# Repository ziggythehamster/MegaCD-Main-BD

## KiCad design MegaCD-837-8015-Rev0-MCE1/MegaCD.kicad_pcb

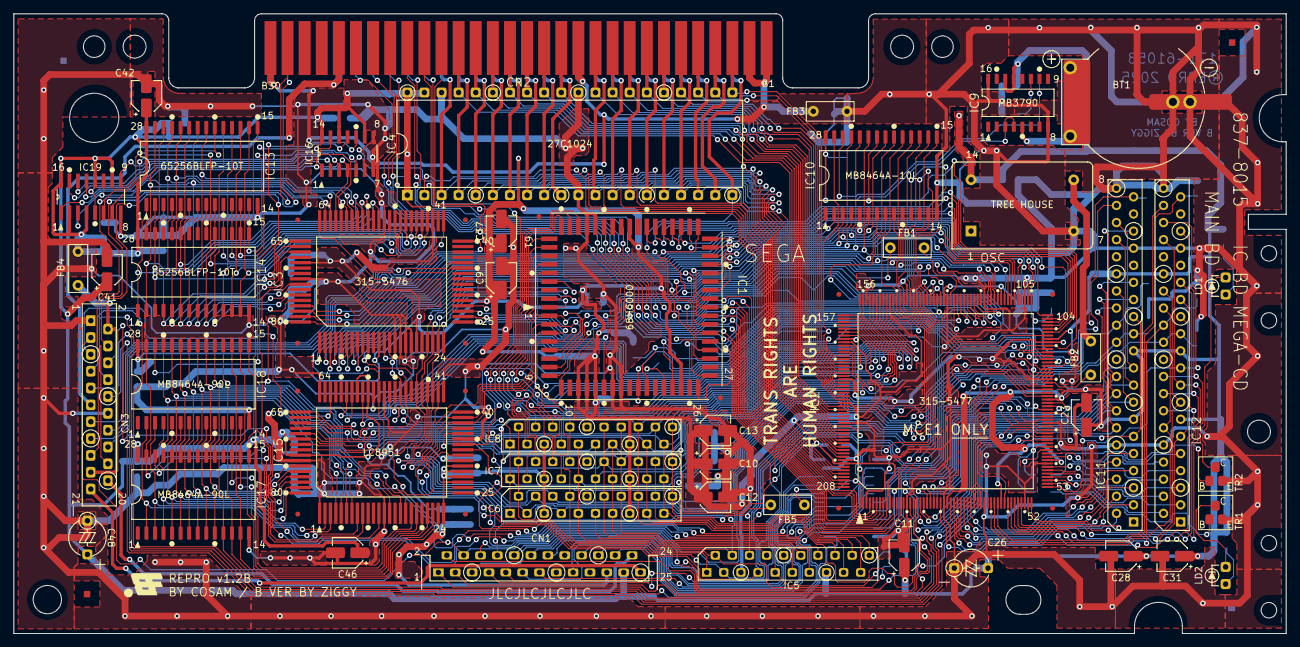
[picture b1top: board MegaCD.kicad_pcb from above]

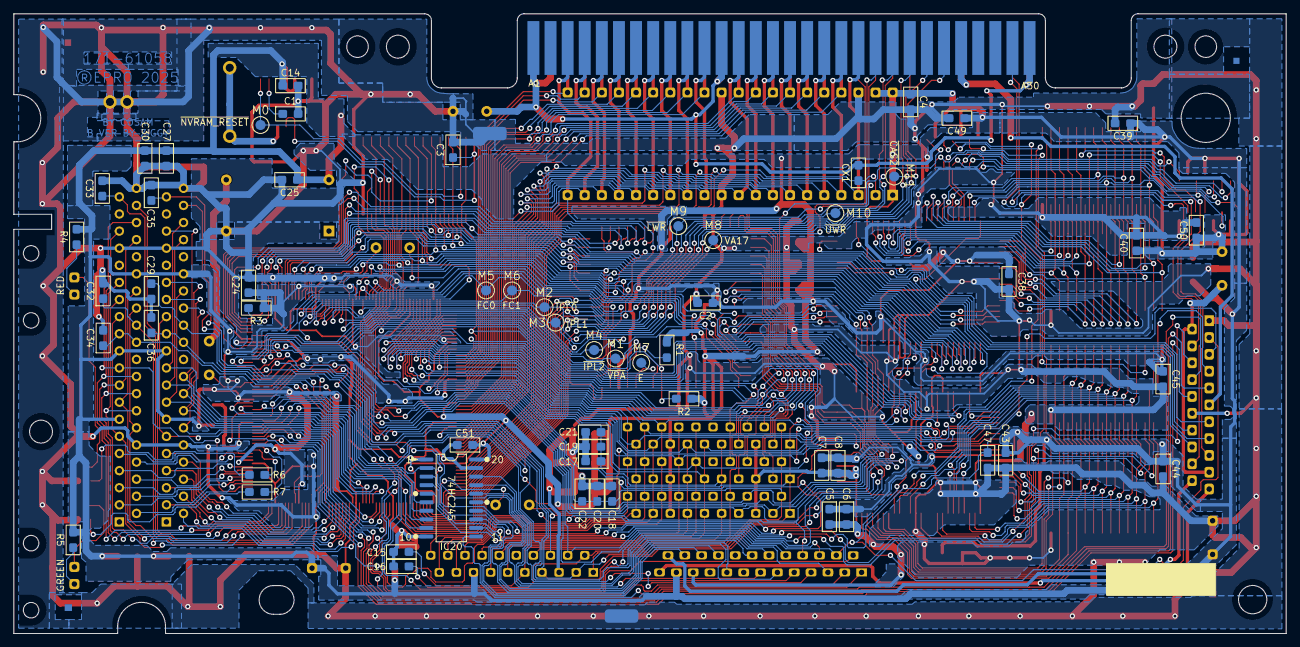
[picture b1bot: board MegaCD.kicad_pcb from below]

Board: 6 copper layers, 188.9 x 92.0 mm, 107 parts (60 on the bottom side), 274 nets.

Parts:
BT1: AL2032; Battery
C1: 1000pF; SMD_0805_HandSolder_Medium
C2, C3, C4, C5, C6, C7, C8, C14, C24, C25, C27, C30, C38, C39, C40, C43, C44, C45, C49, C50, C51: 22nF; SMD_0805_HandSolder_Medium
C9, C10, C11, C12, C13, C23, C28, C31, C37, C41, C42, C46: 10uF; CP_Elec_4x5.4
C15, C16, C17, C18, C19, C20, C21, C22, C33, C35, C47: Not used; SMD_0805_HandSolder_Medium
C26, C48: 100uF; C_Radial_5mm
C29, C32, C34, C36: 100pF; SMD_0805_HandSolder_Medium
CN1: CON 25P ANGLE; CON-25P-ANGLE
CN2: EDGE 60P; EDGE-60P
CN3: CON 21P; CON-21P
CX1: 51pF; SMD_0805_HandSolder_Medium
FB1, FB2, FB5: FB; FB_P5.00mm
FB3: WIRE LINK; FB_P5.00mm
FB4: FBA04; FB_P5.00mm
G1, G2: Ground_Link
IC1: 68HC000; PLCC-68-Longer_Pads
IC2: 315-5477; PQFP-208_28x28mm_P0.5mm
IC3: 315-5476; PQFP-80_14x20mm_P0.8mm_long_pads
IC4: 27C1024; DIP-40_W15.24mm_Socket
IC5, IC6, IC7, IC8: MB81C4256Z; ZIP-20
IC9: MB3790; SOIC-16W_5.3x10.2mm_P1.27mm
IC10: MB8464A-10L; SOIC-28Wider
IC11, IC12: TC511664BZ; ZIP-40
IC13, IC14: 65256BLFP-10T; SOIC-28Wider
IC15: LC8951; PQFP-80_14x20mm_P0.8mm_long_pads
IC16: 74HC00; IC_SN74HC00DR
IC17, IC18: MB8464A-90L; SOIC-28Wider
IC19: 74HC112; IC_SN74HC112DR
IC20: 74HC245; SOIC-20W_7.5x12.8mm_P1.27mm_narrowed
LD1: RED; LED
LD2: GREEN; LED
M0, M1, M2, M3, M4, M5, M6, M7, M8, M9, M10, M11: TestPoint; Test_Point_1.5mm
OSC1: TREE HOUSE; Oscillator_DIP-14
R1, R2, R6, R7: 4.7K; SMD_0805_HandSolder_Medium
R3: 2.2K; SMD_0805_HandSolder_Medium
R4: 360; SMD_0805_HandSolder_Medium
R5: 160; SMD_0805_HandSolder_Medium
TR1, TR2: C1623; SOT-23-Wide

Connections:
12M: FB1.1, IC1.15 (CLK), IC3.70 (XIN)
25M: FB5.2, IC15.25 (XTALCK)
50M: FB2.2, IC2.84 (50M)
/12MF: FB1.2, IC2.129 (12M)
/25MF: FB5.1, IC2.1 (25M)
/50MF: FB2.1, OSC1.8 (OUT)
/BATPW: C1.1, IC9.11 (CT)
/C2PO: CN1.10, IC2.77 (C2PO)
/CD0: IC15.23 (IO1), IC17.11 (D0), IC18.11 (D0)
/CD1: IC15.22 (IO2), IC17.12 (D1), IC18.12 (D1)
/CD2: IC15.21 (IO3), IC17.13 (D2), IC18.13 (D2)
/CD3: IC15.20 (IO4), IC17.15 (D3), IC18.15 (D3)
/CD4: IC15.19 (IO5), IC17.16 (D4), IC18.16 (D4)
/CD5: IC15.18 (IO6), IC17.17 (D5), IC18.17 (D5)
/CD6: IC15.17 (IO7), IC17.18 (D6), IC18.18 (D6)
/CD7: IC15.16 (IO8), IC17.19 (D7), IC18.19 (D7)
/DB0: CN1.6, IC2.82 (DB0)
/DB1: CN1.7, IC2.81 (DB1)
/DB2: CN1.8, IC2.80 (DB2)
/DB3: CN1.9, IC2.78 (DB3)
/D/M: CN1.2, IC2.87 (D/M)
/EAD0: IC2.17 (EAD0), IC11.11 (D0), IC11.25 (A0)
/EAD1: IC2.18 (EAD1), IC11.12 (D1), IC11.26 (A1)
/EAD2: IC2.19 (EAD2), IC11.14 (D2), IC11.27 (A2)
/EAD3: IC2.20 (EAD3), IC11.15 (D3), IC11.28 (A3)
/EAD4: IC2.21 (EAD4), IC11.16 (D4), IC11.29 (A4)
/EAD5: IC2.22 (EAD5), IC11.17 (D5), IC11.34 (A5)
/EAD6: IC2.23 (EAD6), IC11.18 (D6), IC11.35 (A6)
/EAD7: IC2.24 (EAD7), IC11.19 (D7), IC11.36 (A7)
/ED8: IC2.25 (ED8), IC11.2 (D8)
/ED9: IC2.28 (ED9), IC11.3 (D9)
/ED10: IC2.29 (ED10), IC11.4 (D10)
/ED11: IC2.30 (ED11), IC11.5 (D11)
/ED12: IC2.31 (ED12), IC11.6 (D12)
/ED13: IC2.32 (ED13), IC11.7 (D13)
/ED14: IC2.33 (ED14), IC11.8 (D14)
/ED15: IC2.34 (ED15), IC11.9 (D15)
/EXCK: CN1.17, IC2.74 (EXCK)
/HDCK: CN1.5, IC2.83 (HDCK)
/LD1A: LD1.2 (A), R4.1
/LD1K: LD1.1 (K), TR2.3 (C)
/LD1TRB: R6.2, TR2.1 (B)
/LD2A: LD2.2 (A), R5.1
/LD2K: LD2.1 (K), TR1.3 (C)
/LD2TRB: R7.2, TR1.1 (B)
/LEDG: IC2.65 (LEDG), R7.1
/LEDR: IC2.64 (LEDR), R6.1
/NVRAM_VCC: C3.1, IC9.3 (VOUT), IC9.4 (VOUT), IC10.28 (VCC)
/OAD0: IC2.45 (OAD0), IC12.11 (D0), IC12.25 (A0)
/OAD1: IC2.46 (OAD1), IC12.12 (D1), IC12.26 (A1)
/OAD2: IC2.47 (OAD2), IC12.14 (D2), IC12.27 (A2)
/OAD3: IC2.48 (OAD3), IC12.15 (D3), IC12.28 (A3)
/OAD4: IC2.49 (OAD4), IC12.16 (D4), IC12.29 (A4)
/OAD5: IC2.51 (OAD5), IC12.17 (D5), IC12.34 (A5)
/OAD6: IC2.52 (OAD6), IC12.18 (D6), IC12.35 (A6)
/OAD7: IC2.53 (OAD7), IC12.19 (D7), IC12.36 (A7)
/OD8: IC2.54 (OD8), IC12.2 (D8)
/OD9: IC2.55 (OD9), IC12.3 (D9)
/OD10: IC2.56 (OD10), IC12.4 (D10)
/OD11: IC2.57 (OD11), IC12.5 (D11)
/OD12: IC2.58 (OD12), IC12.6 (D12)
/OD13: IC2.59 (OD13), IC12.7 (D13)
/OD14: IC2.62 (OD14), IC12.8 (D14)
/OD15: IC2.63 (OD15), IC12.9 (D15)
/RA0: IC3.76 (RAMA0), IC13.10 (A0), IC14.10 (A0)
/RA1: IC3.75 (RAMA1), IC13.9 (A1), IC14.9 (A1)
/RA2: IC3.74 (RAMA2), IC13.8 (A2), IC14.8 (A2)
/RA3: IC3.73 (RAMA3), IC13.7 (A3), IC14.7 (A3)
/RA4: IC3.68 (RAMA4), IC13.6 (A4), IC14.6 (A4)
/RA5: IC3.67 (RAMA5), IC13.5 (A5), IC14.5 (A5)
/RA6: IC3.66 (RAMA6), IC13.4 (A6), IC14.4 (A6)
/RA7: IC3.65 (RAMA7), IC13.3 (A7), IC14.3 (A7)
/RA8: IC3.59 (RAMA8), IC13.25 (A8), IC14.25 (A8)
/RA9: IC3.58 (RAMA9), IC13.24 (A9), IC14.24 (A9)
/RA10: IC3.57 (RAMA10), IC13.21 (A10), IC14.21 (A10)
/RA11: IC3.56 (RAMA11), IC13.23 (A11), IC14.23 (A11)
/RA12: IC3.55 (RAMA12), IC13.2 (A12), IC14.2 (A12)
/RA13: IC3.54 (RAMA13), IC13.26 (A13), IC14.26 (A13)
/RA14: IC3.53 (RAMA14), IC13.1 (A14), IC14.1 (A14)
/RAA0: IC15.75 (RA0), IC17.10 (A0), IC18.10 (A0)
/RAA1: IC15.76 (RA1), IC17.9 (A1), IC18.9 (A1)
/RAA2: IC15.77 (RA2), IC17.8 (A2), IC18.8 (A2)
/RAA3: IC15.78 (RA3), IC17.7 (A3), IC18.7 (A3)
/RAA4: IC15.79 (RA4), IC17.6 (A4), IC18.6 (A4)
/RAA5: IC15.80 (RA5), IC17.5 (A5), IC18.5 (A5)
/RAA6: IC15.2 (RA6), IC17.4 (A6), IC18.4 (A6)
/RAA7: IC15.3 (RA7), IC17.3 (A7), IC18.3 (A7)
/RAA8: IC15.4 (RA8), IC17.25 (A8), IC18.25 (A8)
/RAA9: IC15.5 (RA9), IC17.24 (A9), IC18.24 (A9)
/RAA10: IC15.6 (RA10), IC17.21 (A10), IC18.21 (A10)
/RAA11: IC15.7 (RA11), IC17.23 (A11), IC18.23 (A11)
/RAA12: IC15.8 (RA12), IC17.2 (A12), IC18.2 (A12)
/VBAT: BT1.1 (+), IC9.5 (VBAT2)
/VCC2F: CN3.2, CN3.19, FB4.2
/WD0: IC3.51 (RAMAD0), IC13.11 (D0), IC14.11 (D0)
/WD1: IC3.50 (RAMAD1), IC13.12 (D1), IC14.12 (D1)
/WD2: IC3.49 (RAMAD2), IC13.13 (D2), IC14.13 (D2)
/WD3: IC3.48 (RAMAD3), IC13.15 (D3), IC14.15 (D3)
/WD4: IC3.47 (RAMAD4), IC13.16 (D4), IC14.16 (D4)
/WD5: IC3.46 (RAMAD5), IC13.17 (D5), IC14.17 (D5)
/WD6: IC3.45 (RAMAD6), IC13.18 (D6), IC14.18 (D6)
/WD7: IC3.44 (RAMAD7), IC13.19 (D7), IC14.19 (D7)
/~IRQ: CN1.3, IC2.86 (~IRQ)
/~NVRAM_RESET: IC9.10 (~RESET), IC10.26 (CS2), M0.1
/~RCS1N: IC16.3, IC19.15 (~R)
/~RCS1Q: IC16.2, IC19.5 (Q)
/~RCS2N: IC16.6, IC19.14 (~R)
/~RCS2Q: IC16.5, IC19.9 (Q)
/~RCS: IC15.62 (~RCS), IC17.20 (~CS1), IC18.20 (~CS1)
/~ROE8951: IC15.14 (~ROE), IC17.22 (~OE), IC18.22 (~OE)
/~RWE8951: IC15.12 (~RWE), IC17.27 (~WE), IC18.27 (~WE)
/~RWE: IC3.63 (~RWE), IC13.27 (~WE), IC14.27 (~WE)
A1: IC1.32 (A1), IC2.120 (A1), IC3.10 (A0), IC10.10 (A0), IC15.47 (RS)
A2: IC1.33 (A2), IC2.118 (A2), IC3.9 (A1), IC10.9 (A1)
A3: IC1.34 (A3), IC2.117 (A3), IC3.8 (A3), IC10.8 (A2)
A4: IC1.35 (A4), IC2.116 (A4), IC3.7 (A4), IC10.7 (A3)
A5: IC1.36 (A5), IC2.115 (A5), IC3.6 (A5), IC10.6 (A4)
A6: IC1.37 (A6), IC2.113 (A6), IC3.5 (A6), IC10.5 (A5)
A7: IC1.38 (A7), IC2.112 (A7), IC3.4 (A7), IC10.4 (A6)
A8: IC1.39 (A8), IC2.111 (A8), IC3.3 (A8), IC10.3 (A7)
A9: IC1.40 (A9), IC2.110 (A9), IC3.2 (A9), IC10.25 (A8)
A10: IC1.41 (A10), IC2.109 (A10), IC3.1 (A10), IC10.24 (A9)
A11: IC1.42 (A11), IC2.108 (A11), IC3.80 (A11), IC10.21 (A10)
A12: IC1.43 (A12), IC2.106 (A12), IC3.79 (A12), IC10.23 (A11)
A13: IC1.44 (A13), IC2.105 (A13), IC3.78 (A13), IC10.2 (A12), R3.2
A14: IC1.45 (A14), IC2.104 (A14)
A15: IC1.46 (A15), IC2.103 (A15)
A16: IC1.47 (A16), IC2.102 (A16)
A17: IC1.48 (A17), IC2.101 (A17)
A18: IC1.49 (A18), IC2.100 (A18)
A19: IC1.50 (A19), IC2.99 (A19)
ATT: CN3.8, IC2.68 (AT)
BCK: IC15.34 (BCK), IC16.8
BCLK: CN1.11, IC20.15 (B3)
BCLKB: CN3.4, IC16.10, IC20.5 (A3)
C2LR: IC2.98 (C2LR), IC15.36 (C2PO)
CDCK: CN1.1, IC20.11 (B7)
CDCKD: IC2.88 (CDCK), IC20.9 (A7)
D0: IC1.5 (D0), IC2.137 (D0), IC3.28 (D0), IC5.6 (D0), IC10.11 (D0), IC15.38 (D0)
D1: IC1.4 (D1), IC2.138 (D1), IC3.27 (D1), IC5.7 (D1), IC10.12 (D1), IC15.39 (D1)
D2: IC1.3 (D2), IC2.139 (D2), IC3.26 (D2), IC5.3 (D2), IC10.13 (D2), IC15.40 (D2)
D3: IC1.2 (D3), IC2.140 (D3), IC3.25 (D3), IC5.4 (D3), IC10.15 (D3), IC15.42 (D3)
D4: IC1.1 (D4), IC2.141 (D4), IC3.24 (D4), IC6.6 (D0), IC10.16 (D4), IC15.43 (D4)
D5: IC1.68 (D5), IC2.143 (D5), IC3.23 (D5), IC6.7 (D1), IC10.17 (D5), IC15.44 (D5)
D6: IC1.67 (D6), IC2.144 (D6), IC3.22 (D6), IC6.3 (D2), IC10.18 (D6), IC15.45 (D6)
D7: IC1.66 (D7), IC2.145 (D7), IC3.21 (D7), IC6.4 (D3), IC10.19 (D7), IC15.46 (D7)
D8: IC1.65 (D8), IC2.146 (D8), IC7.6 (D0)
D9: IC1.64 (D9), IC2.148 (D9), IC7.7 (D1)
D10: IC1.63 (D10), IC2.149 (D10), IC7.3 (D2)
D11: IC1.62 (D11), IC2.150 (D11), IC7.4 (D3)
D12: IC1.61 (D12), IC2.151 (D12), IC8.6 (D0)
D13: IC1.60 (D13), IC2.152 (D13), IC8.7 (D1)
D14: IC1.59 (D14), IC2.153 (D14), IC8.3 (D2)
D15: IC1.58 (D15), IC2.155 (D15), IC8.4 (D3)
DDATA: CN3.7, IC2.69 (DTM)
DFCK: CN1.14, IC20.17 (B1)
DFCKB: CN3.6, IC20.3 (A1)
E: IC1.22 (E), M7.1
FC0: IC1.30 (FC0), IC2.121 (FC0), M5.1
FC1: IC1.29 (FC1), IC2.122 (FC1), M6.1
FRES: CN2.a25, IC2.14 (FRES)
GND: BT1.2 (-), C1.2, C2.2, C3.2, C4.2, C5.2, C6.2, C7.2, C8.2, C9.2, C10.2, C11.2, C12.2, C13.2, C14.2, C15.2, C16.2, C17.2, C18.2, C19.2, C20.2, C21.2, C22.2, C23.2, C24.2, C25.2, C26.2, C27.2, C28.2, C29.2, C30.2, C31.2, C32.2, C33.2, C34.2, C35.2, C36.2, C37.2, C38.2, C39.2, C40.2, C41.2, C42.2, C43.2, C44.2, C45.2, C46.2, C47.2, C48.2, C49.2, C50.2, C51.2, CN1.21, CN2.a1, CN2.a12, CN2.a30, CN2.b1, CN2.b2, CN2.b12, CN2.b30, CN3.1, CN3.12, CX1.2, FB3.1, FB3.2, G1.1, G2.1, IC1.16 (GND), IC1.17 (GND), IC1.56 (GND), IC1.57 (GND), IC2.3 (VSS), IC2.15 (VSS), IC2.26 (VSS), IC2.38 (VSS), IC2.50 (VSS), IC2.60 (VSS), IC2.72 (VSS), IC2.85 (VSS), IC2.96 (VSS), IC2.107 (VSS), IC2.119 (VSS), IC2.130 (VSS), IC2.142 (VSS), IC2.154 (VSS), IC2.164 (VSS), IC2.176 (VSS), IC2.189 (VSS), IC2.200 (VSS), IC3.15 (GND), IC3.16 (TEST1), IC3.17 (TEST2), IC3.18 (TEST3), IC3.52 (GND), IC3.72 (GND), IC4.11 (GND), IC4.30 (GND), IC4.38 (D.C.), IC5.5 (VSS), IC6.5 (VSS), IC7.5 (VSS), IC8.5 (VSS), IC9.8 (GND), IC9.16 (CONTROL), IC10.14 (GND), IC11.10 (GND), IC11.33 (GND), IC11.40 (GND), IC12.10 (GND), IC12.33 (GND), IC12.40 (GND), IC13.14 (GND), IC14.14 (GND), IC15.1 (VSS), IC15.13 (VSS), IC15.24 (VSS), IC15.27 (TEST1), IC15.28 (TEST2), IC15.29 (CSEL), IC15.30 (LMSEL), IC15.35 (VSS), IC15.41 (VSS), IC15.52 (VSS), IC15.54 (~ENABLE), IC15.64 (VSS), IC15.74 (SELDRQ), IC16.7 (GND), IC17.14 (GND), IC18.14 (GND), IC19.8 (GND), IC20.1 (A->B), IC20.10 (GND), IC20.19 (CE), OSC1.7 (GND), TR1.2 (E), TR2.2 (E)
LATCH: CN3.10, IC2.66 (LATCH)
LRCK: CN1.13, IC20.16 (B2)
LRCKB: C47.1, CN3.5, IC2.75 (LRCK), IC15.32 (LRCK), IC20.4 (A2)
M.GND: CN1.25, CN3.21
M.VCC: CN1.24, CN3.20
PA0: IC2.156 (PA0), IC5.11 (A0), IC6.11 (A0), IC7.11 (A0), IC8.11 (A0), IC15.72 (HD0)
PA1: IC2.157 (PA1), IC5.12 (A1), IC6.12 (A1), IC7.12 (A1), IC8.12 (A1), IC15.71 (HD1)
PA2: IC2.158 (PA2), IC5.13 (A2), IC6.13 (A2), IC7.13 (A2), IC8.13 (A2), IC15.70 (HD2)
PA3: IC2.159 (PA3), IC5.14 (A3), IC6.14 (A3), IC7.14 (A3), IC8.14 (A3), IC15.69 (HD3)
PA4: IC2.160 (PA4), IC5.16 (A4), IC6.16 (A4), IC7.16 (A4), IC8.16 (A4), IC15.68 (HD4)
PA5: IC2.161 (PA5), IC5.17 (A5), IC6.17 (A5), IC7.17 (A5), IC8.17 (A5), IC15.67 (HD5)
PA6: IC2.162 (PA6), IC5.18 (A6), IC6.18 (A6), IC7.18 (A6), IC8.18 (A6), IC15.66 (HD6)
PA7: IC2.163 (PA7), IC5.19 (A7), IC6.19 (A7), IC7.19 (A7), IC8.19 (A7), IC15.65 (HD7)
PA8: IC2.166 (PA8), IC5.20 (A8), IC6.20 (A8), IC7.20 (A8), IC8.20 (A8)
PBCLK: CN3.15, IC3.35 (BCLK)
PDATA: CN3.13, IC3.36 (DATA)
PLRCK: CN3.16, IC3.40 (LRCK)
PWCLK: CN3.14, IC3.41 (WCLK1)
R/~W: IC1.9 (R/W), IC2.133 (R/~W)
SBSO: CN1.18, IC20.14 (B4)
SBSOB: IC2.73 (SBSO), IC20.6 (A4)
SCOR: CN1.20, IC20.13 (B5)
SCORB: IC2.71 (SCOR), IC20.7 (A5)
SDATA: CN1.12, IC20.18 (B0)
SDATAB: IC2.76 (SDATA), IC15.33 (SDATA), IC20.2 (A0)
SHFT: CN3.9, IC2.67 (SHFT)
SL2: CN2.b29, CN3.17
SR2: CN2.a29, CN3.18
VA1: CN2.b3, IC2.171 (VA1), IC4.21 (A0)
VA2: CN2.b4, IC2.172 (VA2), IC4.22 (A1)
VA3: CN2.b5, IC2.173 (VA3), IC4.23 (A2)
VA4: CN2.b6, IC2.174 (VA4), IC4.24 (A3)
VA5: CN2.b7, IC2.175 (VA5), IC4.25 (A4)
VA6: CN2.b8, IC2.177 (VA6), IC4.26 (A5)
VA7: CN2.b9, IC2.178 (VA7), IC4.27 (A6)
VA8: CN2.b10, IC2.179 (VA8), IC4.28 (A7)
VA9: CN2.b11, IC2.180 (VA9), IC4.29 (A8)
VA10: CN2.b13, IC2.181 (VA10), IC4.31 (A9)
VA11: CN2.b14, IC2.182 (VA11), IC4.32 (A10)
VA12: CN2.b15, IC2.184 (VA12), IC4.33 (A11)
VA13: CN2.b16, IC2.185 (VA13), IC4.34 (A12)
VA14: CN2.b17, IC2.186 (VA14), IC4.35 (A13)
VA15: CN2.b18, IC2.187 (VA15), IC4.36 (A14)
VA16: CN2.b19, IC2.188 (VA16), IC4.37 (A15)
VA17: CN2.b20, IC2.190 (VA17), M8.1
VCC: CN2.a26, CN2.b26, CN3.11
VCC2: C2.1, C4.1, C5.1, C6.1, C7.1, C8.1, C9.1, C10.1, C11.1, C12.1, C13.1, C14.1, C23.1, C24.1, C25.1, C26.1, C27.1, C28.1, C30.1, C31.1, C37.1, C38.1, C39.1, C40.1, C41.1, C42.1, C43.1, C44.1, C45.1, C46.1, C48.1, C49.1, C50.1, C51.1, CN1.23, FB4.1, IC1.12 (BGACK), IC1.13 (BR), IC1.14 (VCC), IC1.24 (BERR), IC1.52 (VCC), IC2.10 (VDD), IC2.27 (VDD), IC2.43 (VDD), IC2.61 (VDD), IC2.79 (VDD), IC2.97 (VDD), IC2.114 (VDD), IC2.131 (VDD), IC2.147 (VDD), IC2.165 (VDD), IC2.183 (VDD), IC2.201 (VDD), IC3.12 (VCC), IC3.19 (VCC), IC3.43 (VCC), IC3.69 (VCC), IC4.1 (VPP), IC4.39 (~PGM), IC4.40 (VCC), IC5.15 (VCC), IC6.15 (VCC), IC7.15 (VCC), IC8.15 (VCC), IC9.13 (VIN), IC9.14 (VIN), IC11.13 (VCC), IC11.21 (VCC), IC11.30 (VCC), IC12.13 (VCC), IC12.21 (VCC), IC12.30 (VCC), IC13.28 (VCC), IC14.28 (VCC), IC15.31 (VDD), IC15.55 (~HWR), IC15.57 (~CMD), IC15.73 (VDD), IC16.9, IC16.12, IC16.14 (VCC), IC17.28 (VCC), IC18.28 (VCC), IC19.2 (K), IC19.4 (~S), IC19.10 (~S), IC19.12 (K), IC19.16 (VCC), IC20.20 (VCC), OSC1.14 (Vcc), R1.1, R2.1, R3.1, R4.2, R5.2
VD0: CN2.a4, IC2.191 (VD0), IC4.19 (D0)
VD1: CN2.a5, IC2.192 (VD1), IC4.18 (D1)
VD2: CN2.a6, IC2.193 (VD2), IC4.17 (D2)
VD3: CN2.a7, IC2.194 (VD3), IC4.16 (D3)
VD4: CN2.a8, IC2.195 (VD4), IC4.15 (D4)
VD5: CN2.a9, IC2.196 (VD5), IC4.14 (D5)
VD6: CN2.a10, IC2.197 (VD6), IC4.13 (D6)
VD7: CN2.a11, IC2.198 (VD7), IC4.12 (D7)
VD8: CN2.a13, IC2.199 (VD8), IC4.10 (D8)
VD9: CN2.a14, IC2.202 (VD9), IC4.9 (D9)
VD10: CN2.a15, IC2.203 (VD10), IC4.8 (D10)
VD11: CN2.a16, IC2.204 (VD11), IC4.7 (D11)
VD12: CN2.a17, IC2.205 (VD12), IC4.6 (D12)
VD13: CN2.a18, IC2.206 (VD13), IC4.5 (D13)
VD14: CN2.a19, IC2.207 (VD14), IC4.4 (D14)
VD15: CN2.a20, IC2.208 (VD15), IC4.3 (D15)
WFCK: CN1.22, IC20.12 (B6)
WFCKD: IC2.70 (WFCK), IC20.8 (A6)
~ASEL: CN2.a22, IC2.9 (~ASEL)
~AS: IC1.6 (AS), IC2.136 (~AS)
~BRAM: IC2.2 (~BRAM), IC10.20 (~CS1)
~BROM: CX1.1, IC2.4 (~BROM), IC4.2 (~CE)
~CAS0: CN2.a3, IC2.6 (~CAS0), IC4.20 (~OE)
~CAS2: CN2.b23, IC2.12 (~CAS2), M11.1
~CDC: IC2.94 (~CDC), IC15.50 (~CS)
~CLWEX: IC2.170 (~CLWE), IC3.14 (~WR), IC5.8 (~WE), IC6.8 (~WE), IC10.27 (~WE), IC15.49 (~WR)
~COE: IC2.95 (~COE), IC3.13 (~RD), IC5.1 (~OE), IC6.1 (~OE), IC7.1 (~OE), IC8.1 (~OE), IC10.22 (~OE), IC15.48 (~RD)
~CUWE: IC2.169 (~CUWE), IC7.8 (~WE), IC8.8 (~WE)
~DTAK: IC1.10 (DTACK), IC2.132 (~DTAK)
~DTEN: IC2.90 (~DTEN), IC15.59 (~DTEN)
~ECAS: C35.1, IC2.36 (~ECAS), IC11.39 (~CAS)
~EOE: IC2.37 (~EOE), IC11.38 (~OE)
~ERAS: C29.1, IC2.35 (~ERAS), IC11.24 (~RAS)
~ERES: CN1.4, CN3.3, IC2.16 (~ERES), IC3.64 (~RES), IC15.53 (~RESET)
~EWE: C36.1, IC2.39 (~EWE), IC11.22 (~UWE), IC11.23 (~LWE)
~FDC: CN2.a24, IC2.13 (~FDC)
~HALT: IC1.19 (HALT), IC2.128 (~HALT), R2.2
~HRD: IC2.92 (~HRD), IC15.56 (~HRD)
~INT: IC2.93 (~INT), IC15.51 (~INT)
~IPL0: IC1.27 (IPL0), IC2.123 (~IPL0), M2.1
~IPL1: IC1.26 (IPL1), IC2.124 (~IPL1), M3.1
~IPL2: IC1.25 (IPL2), IC2.125 (~IPL2), M4.1
~LDS: IC1.8 (LDS), IC2.134 (~LDS)
~LWR: CN2.b21, IC2.7 (~LWR), M9.1
~OCAS: C33.1, IC2.41 (~OCAS), IC12.39 (~CAS)
~OOE: IC2.42 (~OOE), IC12.38 (~OE)
~ORAS: C32.1, IC2.40 (~ORAS), IC12.24 (~RAS)
~OWE: C34.1, IC2.44 (~OWE), IC12.22 (~UWE), IC12.23 (~LWE)
~PCAS: C16.1, C18.1, C20.1, C22.1, IC2.168 (~PCAS), IC5.2 (~CAS), IC6.2 (~CAS), IC7.2 (~CAS), IC8.2 (~CAS)
~PCM: IC2.89 (~PCM), IC3.77 (~CS)
~PRAS: C15.1, C17.1, C19.1, C21.1, IC2.167 (~PRAS), IC5.9 (~RAS), IC6.9 (~RAS), IC7.9 (~RAS), IC8.9 (~RAS)
~RAACS1: IC15.9 (RA13), IC16.13, IC17.26 (CS2)
~RAACS2: IC16.11, IC18.26 (CS2)
~RAS2X: CN2.a23, IC2.11 (~RAS2)
~RCS1X: IC13.20 (~CE), IC19.6 (~Q)
~RCS1: IC3.60 (~RCS1), IC16.1, IC19.1 (C)
~RCS2X: IC14.20 (~CE), IC19.7 (~Q)
~RCS2: IC3.61 (~RCS2), IC16.4, IC19.13 (C)
~RES: IC1.20 (RESET), IC2.127 (~RESET), R1.2
~ROE: IC3.62 (~ROE), IC13.22 (~OE), IC14.22 (~OE), IC19.3 (J), IC19.11 (J)
~ROM: CN2.a21, IC2.5 (~ROM)
~UDS: IC1.7 (UDS), IC2.135 (~UDS)
~UWR: CN2.b22, IC2.8 (~UWR), M10.1
~VPA: IC1.23 (VPA), IC2.126 (~VPA), M1.1
~WAIT: IC2.91 (~WAIT), IC15.58 (~WAIT)

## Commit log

2025-06-17 Add 3D models, fix footprints for JLC manufacture
2025-06-17 Improve board design by making it possible to mostly manufacture at JLCPCB
